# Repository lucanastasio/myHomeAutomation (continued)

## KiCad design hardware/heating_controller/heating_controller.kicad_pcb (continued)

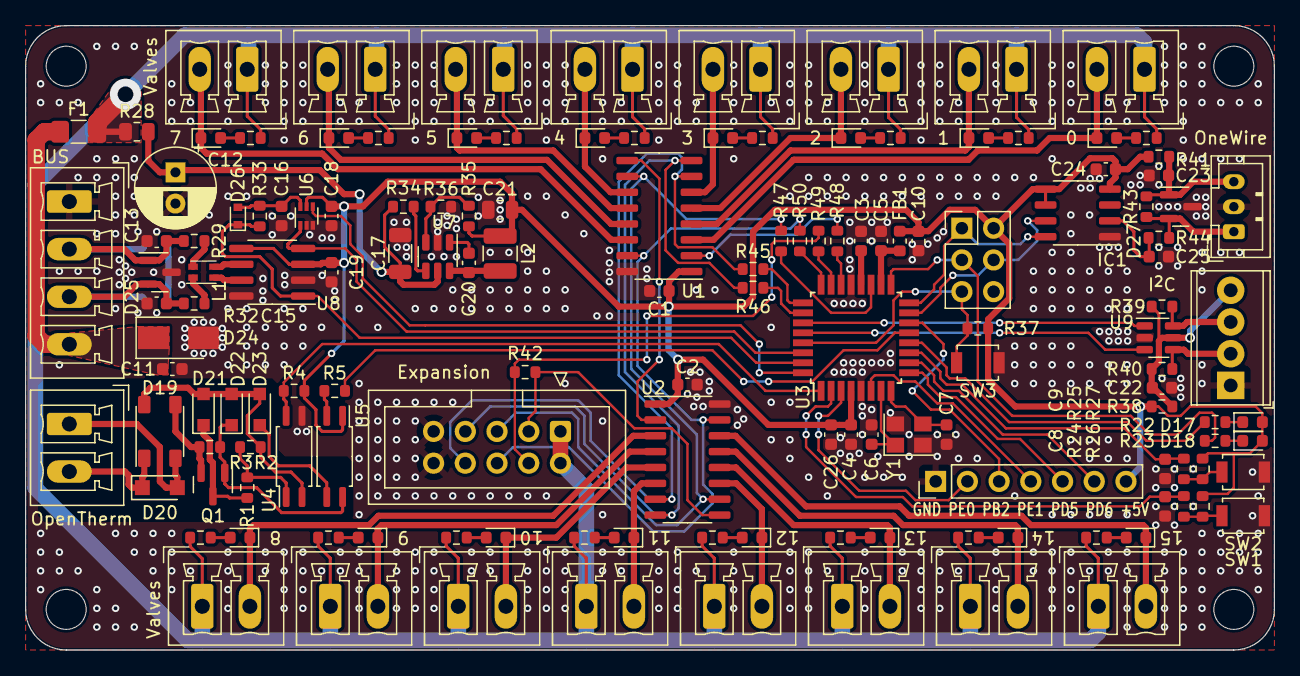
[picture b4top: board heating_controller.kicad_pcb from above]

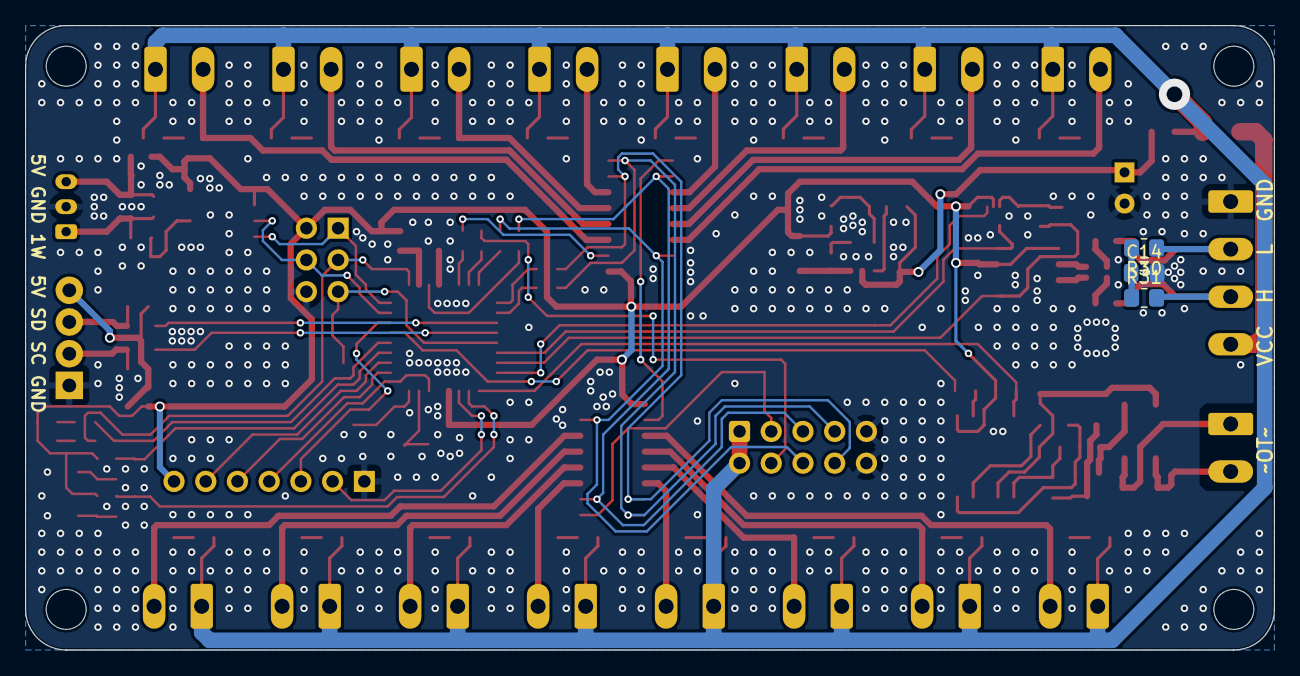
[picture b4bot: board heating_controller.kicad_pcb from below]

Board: 2 copper layers, 100.0 x 50.0 mm, 149 parts (3 on the bottom side), 105 nets.

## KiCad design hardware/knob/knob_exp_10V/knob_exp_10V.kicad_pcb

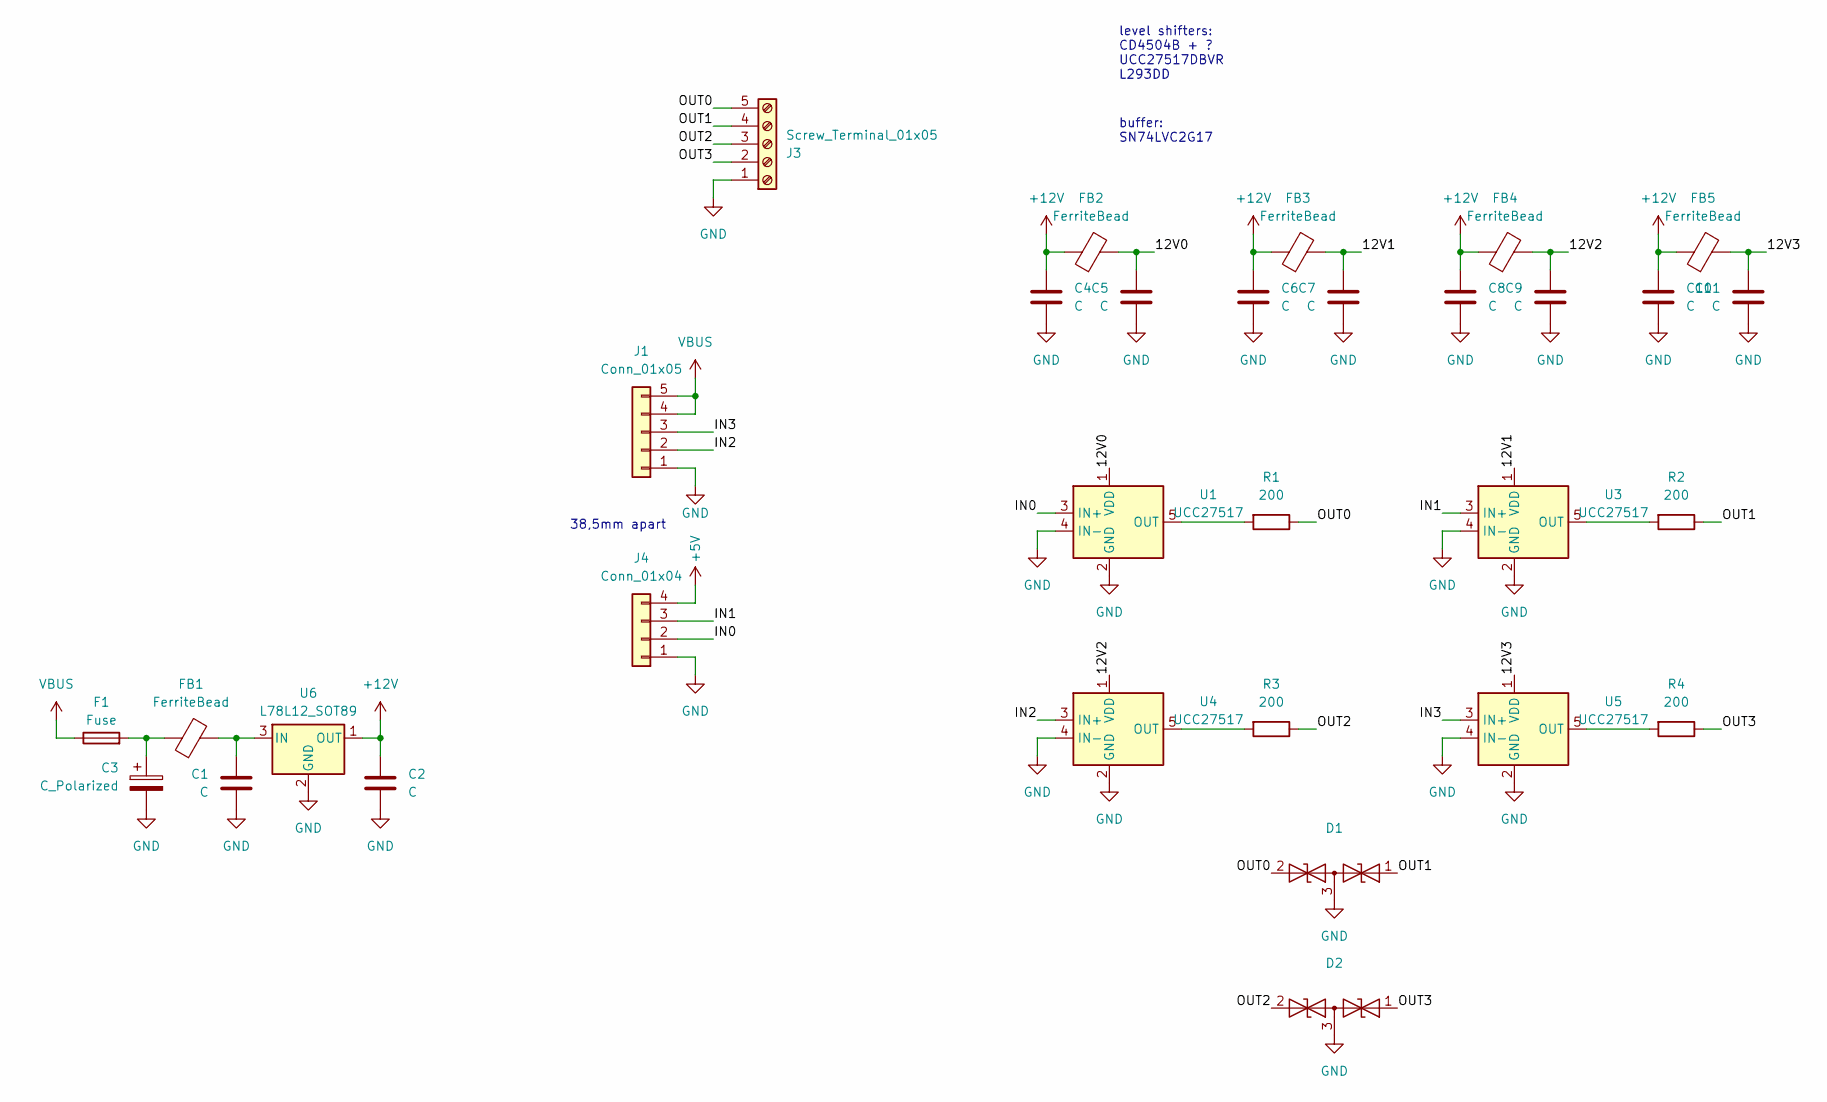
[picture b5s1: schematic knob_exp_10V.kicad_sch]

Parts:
C1: C; C_1206_3216Metric
C2: C; C_0805_2012Metric
C3: C_Polarized; CP_Radial_D6.3mm_P2.50mm
C4, C5, C6, C7, C8, C9, C10, C11: C; C_0603_1608Metric
D1, D2: SOT-23_Handsoldering
F1: Fuse; Fuse_0805_2012Metric_Pad1.15x1.40mm_HandSolder
FB1: FerriteBead; L_1206_3216Metric
FB2, FB3, FB4, FB5: FerriteBead; L_0603_1608Metric
J1: Conn_01x05; PinHeader_1x05_P2.54mm_Vertical
J3: Screw_Terminal_01x05; PhoenixContact_MCV_1,5_5-G-3.81_1x05_P3.81mm_Vertical
J4: Conn_01x04; PinHeader_1x04_P2.54mm_Vertical
R1, R2, R3, R4: 200; R_0603_1608Metric
U1, U3, U4, U5: UCC27517; SOT-23-5
U6: L78L12_SOT89; SOT-89-3

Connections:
+5V: J4.4
+12V: C2.1, C4.1, C6.1, C8.1, C10.1, FB2.1, FB3.1, FB4.1, FB5.1, U6.1 (OUT)
/12V0: C5.2, FB2.2, U1.1 (VDD)
/12V1: C7.2, FB3.2, U3.1 (VDD)
/12V2: C9.2, FB4.2, U4.1 (VDD)
/12V3: C11.2, FB5.2, U5.1 (VDD)
/IN0: J4.2, U1.3 (IN+)
/IN1: J4.3, U3.3 (IN+)
/IN2: J1.2, U4.3 (IN+)
/IN3: J1.3, U5.3 (IN+)
/OUT0: D1.2 (A2), J3.5, R1.1
/OUT1: D1.1 (A1), J3.4, R2.1
/OUT2: D2.2 (A2), J3.3, R3.1
/OUT3: D2.1 (A1), J3.2, R4.1
GND: C1.1, C2.2, C3.2, C4.2, C5.1, C6.2, C7.1, C8.2, C9.1, C10.2, C11.1, D1.3 (common), D2.3 (common), J1.1, J3.1, J4.1, U1.2 (GND), U1.4 (IN-), U3.2 (GND), U3.4 (IN-), U4.2 (GND), U4.4 (IN-), U5.2 (GND), U5.4 (IN-), U6.2 (GND)
unnamed: C3.1, F1.2, FB1.1
unnamed: R1.2, U1.5 (OUT)
unnamed: R2.2, U3.5 (OUT)
unnamed: R3.2, U4.5 (OUT)
unnamed: R4.2, U5.5 (OUT)
unnamed: C1.2, FB1.2, U6.3 (IN)
VBUS: F1.1, J1.4, J1.5

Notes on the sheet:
38,5mm apart
buffer: SN74LVC2G17
level shifters: CD4504B + ? UCC27517DBVR L293DD

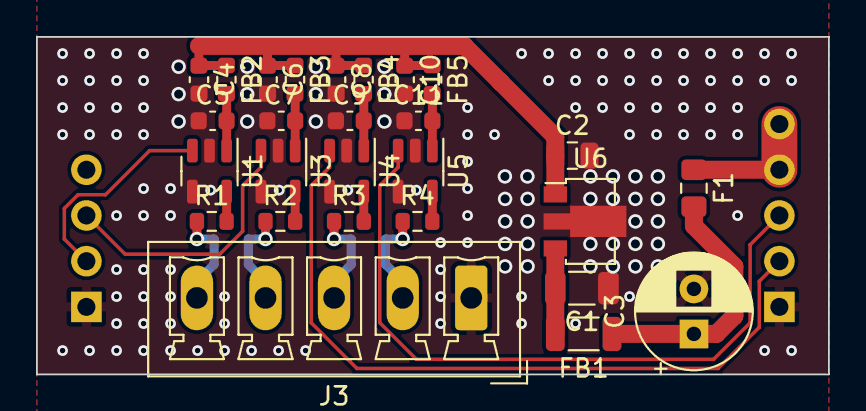
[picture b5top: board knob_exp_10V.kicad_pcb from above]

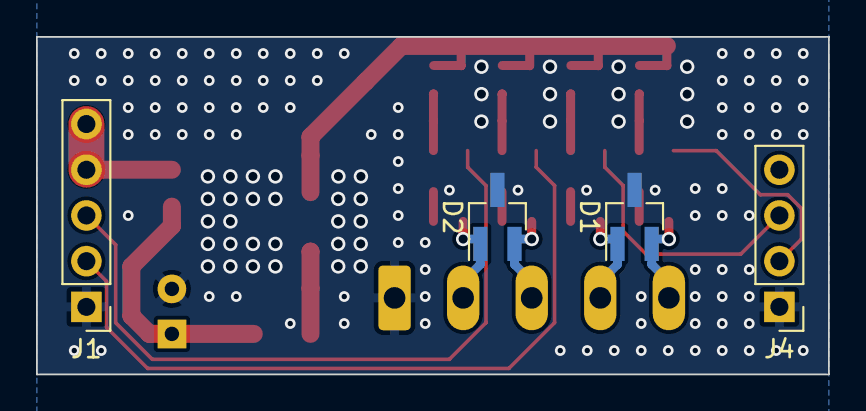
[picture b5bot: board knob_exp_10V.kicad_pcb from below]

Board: 2 copper layers, 44.0 x 18.8 mm, 31 parts (4 on the bottom side), 21 nets.

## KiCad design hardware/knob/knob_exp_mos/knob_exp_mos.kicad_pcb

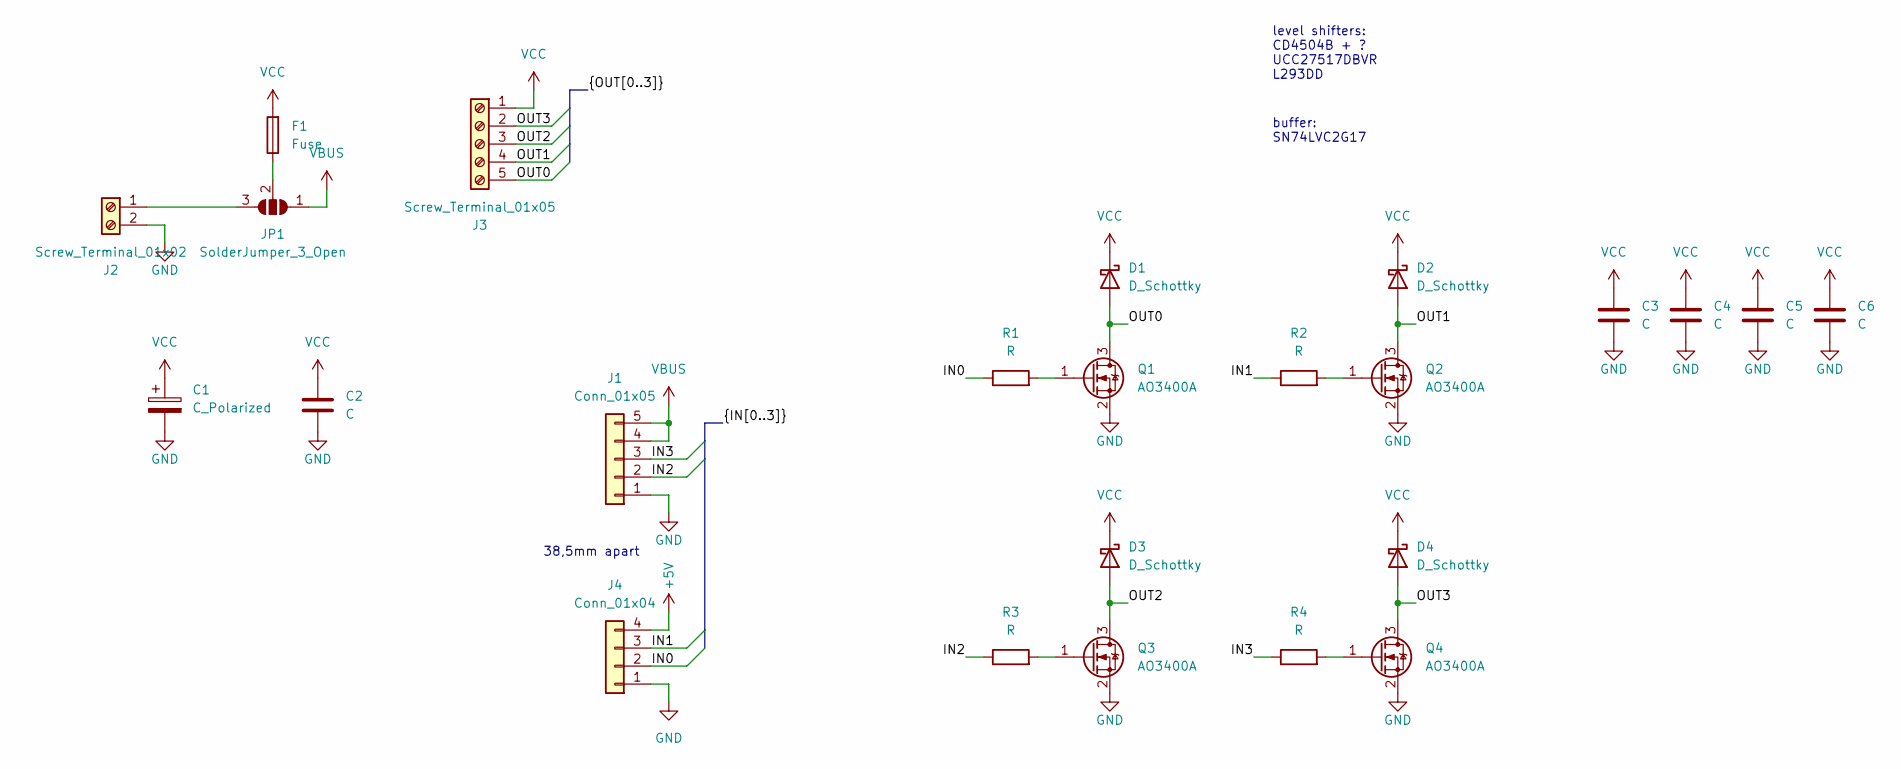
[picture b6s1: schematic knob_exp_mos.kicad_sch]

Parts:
C1: C_Polarized; CP_horizontal_D10.0mm_L20mm_P5.00mm_1
C2: C; C_1206_3216Metric
C3, C4, C5, C6: C; C_0603_1608Metric
D1, D2, D3, D4: D_Schottky; D_TUMD2
F1: Fuse; Fuseholder_Littelfuse_Nano2_154x
J1: Conn_01x05; PinHeader_1x05_P2.54mm_Vertical
J2: Screw_Terminal_01x02; PhoenixContact_MCV_1,5_2-G-3.81_1x02_P3.81mm_Vertical
J3: Screw_Terminal_01x05; PhoenixContact_MCV_1,5_5-G-3.81_1x05_P3.81mm_Vertical
J4: Conn_01x04; PinHeader_1x04_P2.54mm_Vertical
JP1: SolderJumper_3_Open; SolderJumper-3_P2.0mm_Open_Pad1.75x1.75mm
Q1, Q2, Q3, Q4: AO3400A; SOT-23
R1, R2, R3, R4: R; R_0603_1608Metric

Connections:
+5V: J4.4
/IN0: J4.2, R1.1
/IN1: J4.3, R2.1
/IN2: J1.2, R3.1
/IN3: J1.3, R4.1
/OUT0: D1.2 (A), J3.5, Q1.3 (D)
/OUT1: D2.2 (A), J3.4, Q2.3 (D)
/OUT2: D3.2 (A), J3.3, Q3.3 (D)
/OUT3: D4.2 (A), J3.2, Q4.3 (D)
GND: C1.2, C2.2, C3.2, C4.2, C5.2, C6.2, J1.1, J2.2, J4.1, Q1.2 (S), Q2.2 (S), Q3.2 (S), Q4.2 (S)
unnamed: J2.1, JP1.3 (B)
unnamed: F1.1, JP1.2 (C)
unnamed: Q1.1 (G), R1.2
unnamed: Q2.1 (G), R2.2
unnamed: Q3.1 (G), R3.2
unnamed: Q4.1 (G), R4.2
VBUS: J1.4, J1.5, JP1.1 (A)
VCC: C1.1, C2.1, C3.1, C4.1, C5.1, C6.1, D1.1 (K), D2.1 (K), D3.1 (K), D4.1 (K), F1.2, J3.1

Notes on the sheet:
level shifters: CD4504B + ? UCC27517DBVR L293DD
38,5mm apart
buffer: SN74LVC2G17

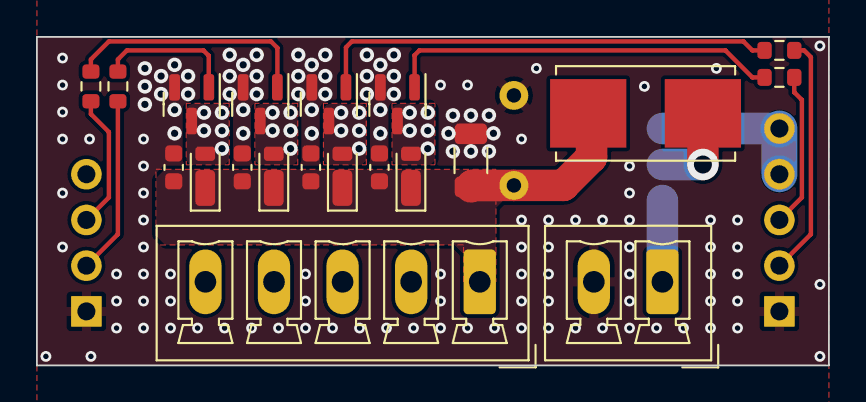
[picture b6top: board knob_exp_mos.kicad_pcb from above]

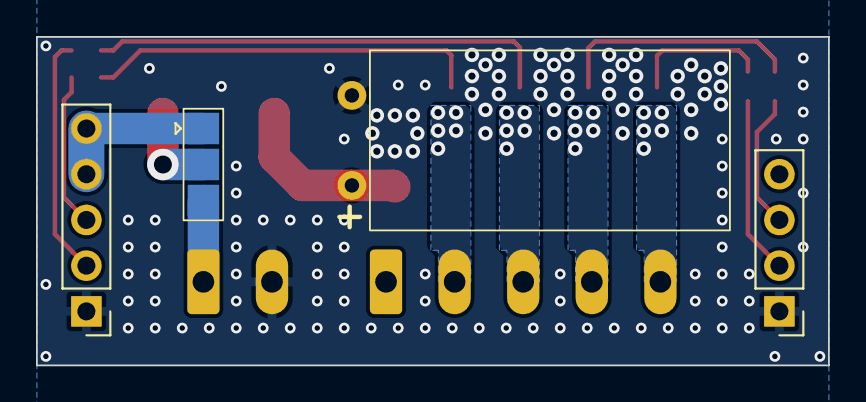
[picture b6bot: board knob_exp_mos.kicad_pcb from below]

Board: 2 copper layers, 44.0 x 18.2 mm, 24 parts (4 on the bottom side), 17 nets.

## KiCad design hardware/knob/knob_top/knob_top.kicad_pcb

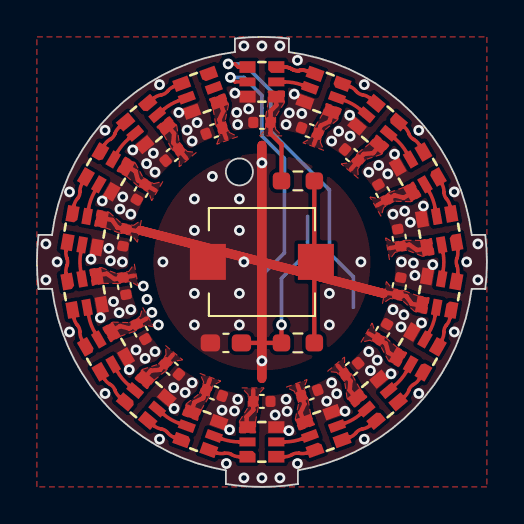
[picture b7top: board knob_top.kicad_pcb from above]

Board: 2 copper layers, 25.0 x 25.0 mm, 41 parts (1 on the bottom side), 40 nets.

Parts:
C1, C2, C3, C4, C5, C6, C7, C8, C9, C10, C11, C12, C13, C14, C15, C16, C17, C18: 100n; C_0402_1005Metric
C19: C; C_0603_1608Metric_Pad1.08x0.95mm_HandSolder
D1, D2, D3, D4, D5, D6, D7, D8, D9, D10, D11, D12, D13, D14, D15, D16, D17, D18: APA102-2020; LED-HD107S-2020_extPads
J1: Conn_02x05_Odd_Even; PinHeader_2x05_P2.54mm_Vertical_SMD
R1, R2: R; R_0603_1608Metric_Pad0.98x0.95mm_HandSolder
SW1: SW_Push; SKPSACE010

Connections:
+5V: C1.1, C2.1, C3.1, C4.1, C5.1, C6.1, C7.1, C8.1, C9.1, C10.1, C11.1, C12.1, C13.1, C14.1, C15.1, C16.1, C17.1, C18.1, D1.1 (VDD), D2.1 (VDD), D3.1 (VDD), D4.1 (VDD), D5.1 (VDD), D6.1 (VDD), D7.1 (VDD), D8.1 (VDD), D9.1 (VDD), D10.1 (VDD), D11.1 (VDD), D12.1 (VDD), D13.1 (VDD), D14.1 (VDD), D15.1 (VDD), D16.1 (VDD), D17.1 (VDD), D18.1 (VDD), J1.2, R1.1
/MOSI: D1.4 (SDI), J1.10
/PB: C19.1, J1.7, R2.2
/SCK: D1.5 (CKI), J1.6
GND: C1.2, C2.2, C3.2, C4.2, C5.2, C6.2, C7.2, C8.2, C9.2, C10.2, C11.2, C12.2, C13.2, C14.2, C15.2, C16.2, C17.2, C18.2, C19.2, D1.6 (GND), D2.6 (GND), D3.6 (GND), D4.6 (GND), D5.6 (GND), D6.6 (GND), D7.6 (GND), D8.6 (GND), D9.6 (GND), D10.6 (GND), D11.6 (GND), D12.6 (GND), D13.6 (GND), D14.6 (GND), D15.6 (GND), D16.6 (GND), D17.6 (GND), D18.6 (GND), J1.1, J1.9, SW1.1
unnamed: D1.2 (CKO), D2.5 (CKI)
unnamed: D1.3 (SDO), D2.4 (SDI)
unnamed: D2.2 (CKO), D3.5 (CKI)
unnamed: D2.3 (SDO), D3.4 (SDI)
unnamed: D3.2 (CKO), D4.5 (CKI)
unnamed: D3.3 (SDO), D4.4 (SDI)
unnamed: D4.2 (CKO), D5.5 (CKI)
unnamed: D4.3 (SDO), D5.4 (SDI)
unnamed: D5.2 (CKO), D6.5 (CKI)
unnamed: D5.3 (SDO), D6.4 (SDI)
unnamed: D6.2 (CKO), D7.5 (CKI)
unnamed: D6.3 (SDO), D7.4 (SDI)
unnamed: D7.2 (CKO), D8.5 (CKI)
unnamed: D7.3 (SDO), D8.4 (SDI)
unnamed: D8.2 (CKO), D9.5 (CKI)
unnamed: D8.3 (SDO), D9.4 (SDI)
unnamed: D9.2 (CKO), D10.5 (CKI)
unnamed: D10.2 (CKO), D11.5 (CKI)
unnamed: D9.3 (SDO), D10.4 (SDI)
unnamed: D10.3 (SDO), D11.4 (SDI)
unnamed: D11.2 (CKO), D12.5 (CKI)
unnamed: D11.3 (SDO), D12.4 (SDI)
unnamed: D12.2 (CKO), D13.5 (CKI)
unnamed: D12.3 (SDO), D13.4 (SDI)
unnamed: D13.2 (CKO), D14.5 (CKI)
unnamed: D13.3 (SDO), D14.4 (SDI)
unnamed: D14.2 (CKO), D15.5 (CKI)
unnamed: D14.3 (SDO), D15.4 (SDI)
unnamed: D15.2 (CKO), D16.5 (CKI)
unnamed: D15.3 (SDO), D16.4 (SDI)
unnamed: D16.2 (CKO), D17.5 (CKI)
unnamed: D16.3 (SDO), D17.4 (SDI)
unnamed: D17.2 (CKO), D18.5 (CKI)
unnamed: D17.3 (SDO), D18.4 (SDI)
unnamed: R1.2, R2.1, SW1.2

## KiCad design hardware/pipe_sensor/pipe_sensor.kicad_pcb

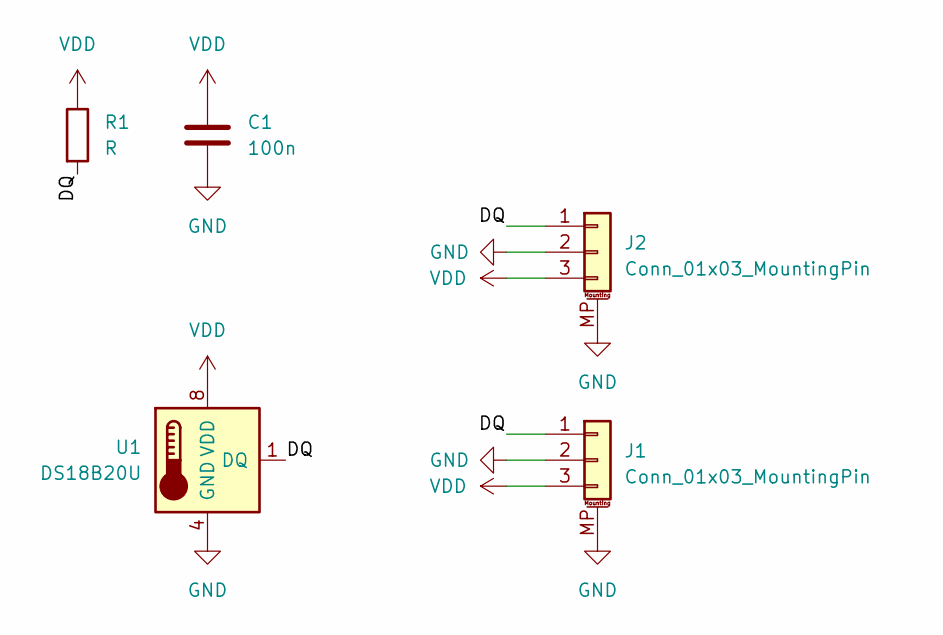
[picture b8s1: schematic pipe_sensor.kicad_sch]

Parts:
C1: 100n; C_0603_1608Metric_Pad1.08x0.95mm_HandSolder
J1, J2: Conn_01x03_MountingPin; JST_SH_SM03B-SRSS-TB_1x03-1MP_P1.00mm_Horizontal
R1: R; R_0603_1608Metric_Pad0.98x0.95mm_HandSolder
U1: DS18B20U; MSOP-8_3x3mm_P0.65mm

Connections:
/DQ: J1.1, J2.1, R1.2, U1.1 (DQ)
GND: C1.2, J1.2, J1.MP (MountPin), J2.2, J2.MP (MountPin), U1.2 (NC), U1.3 (NC), U1.4 (GND), U1.5 (NC), U1.6 (NC), U1.7 (NC)
VDD: C1.1, J1.3, J2.3, R1.1, U1.8 (VDD)

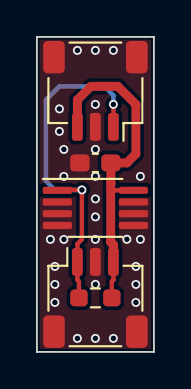
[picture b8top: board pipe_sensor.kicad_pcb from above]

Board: 2 copper layers, 6.5 x 17.5 mm, 5 parts (0 on the bottom side), 3 nets.
